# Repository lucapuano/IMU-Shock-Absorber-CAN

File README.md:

# IMU-Shock-Absorber-CAN
Project of an STM32 based module that controll an electromagnet through CAN protocol and get accelerometer and gyroscope data from an IMU

The project has been made on Kicad 5.1.6

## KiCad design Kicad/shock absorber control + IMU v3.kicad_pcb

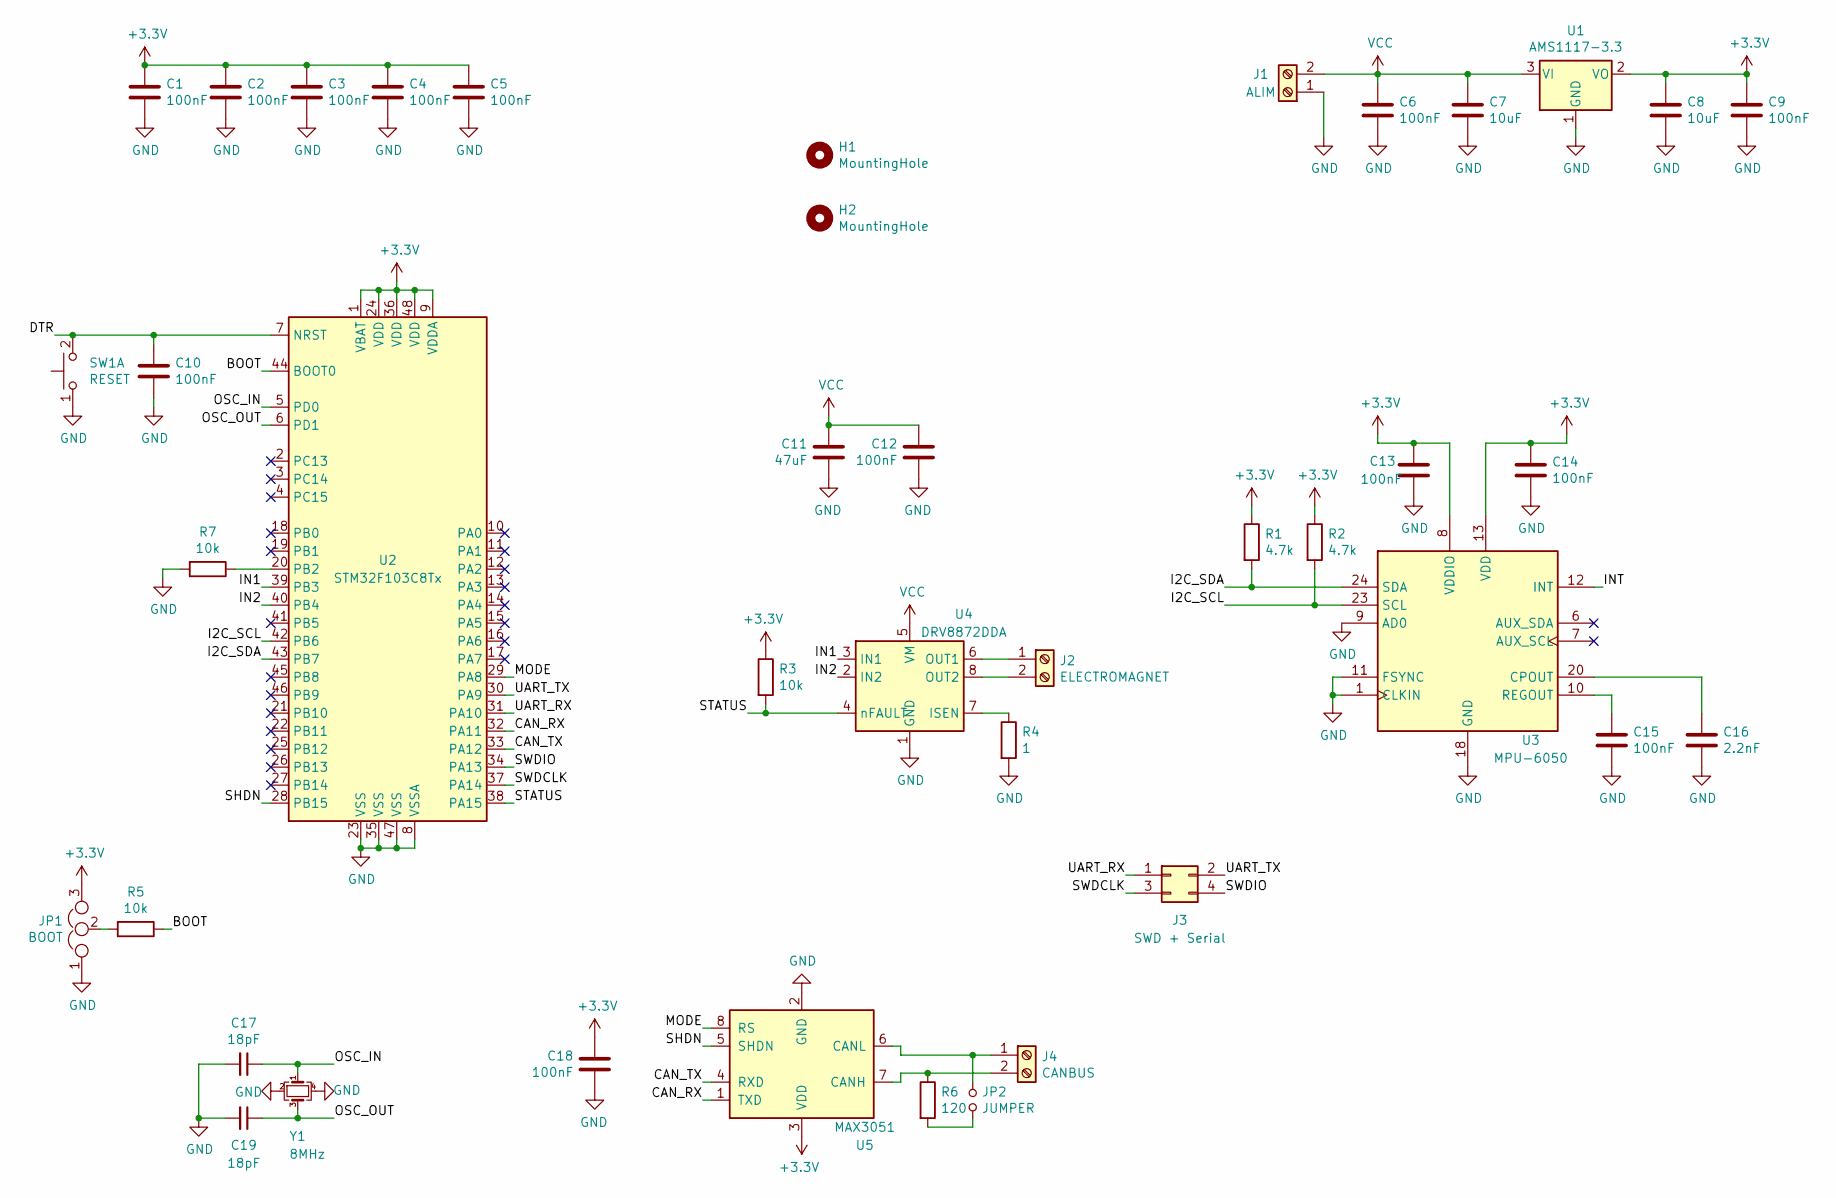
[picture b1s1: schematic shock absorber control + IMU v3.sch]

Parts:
C1, C2, C3, C4, C5, C6, C9, C10, C12, C13, C14, C15, C18: 100nF; C_0603_1608Metric
C7, C8: 10uF; C_0805_2012Metric
C11: 47uF; C_0805_2012Metric
C16: 2.2nF; C_0603_1608Metric
C17, C19: 18pF; C_0603_1608Metric
H1, H2: MountingHole; MountingHole_3mm
J1: ALIM; PinSocket_1x02_P2.54mm_Vertical
J2: ELECTROMAGNET; PinSocket_1x02_P2.54mm_Vertical
J3: SWD + Serial; PinHeader_2x02_P2.54mm_Vertical
J4: CANBUS; PinSocket_1x02_P2.54mm_Vertical
JP1: BOOT; SolderJumper-3_P1.3mm_Open_Pad1.0x1.5mm
JP2: JUMPER; SolderJumper-2_P1.3mm_Open_RoundedPad1.0x1.5mm
R1, R2: 4.7k; R_0603_1608Metric
R3, R5, R7: 10k; R_0603_1608Metric
R4: 1; R_0603_1608Metric
R6: 120; R_0603_1608Metric
SW1: RESET; SW_Push_SPST_NO_Alps_SKRK
U1: AMS1117-3.3; SOT-223-3_TabPin2
U2: STM32F103C8Tx; LQFP-48_7x7mm_P0.5mm
U3: MPU-6050; InvenSense_QFN-24_4x4mm_P0.5mm
U4: DRV8872DDA; HSOP-8-1EP_3.9x4.9mm_P1.27mm_EP2.41x3.1mm_ThermalVias
U5: MAX3051; SOIC-8_3.9x4.9mm_P1.27mm
Y1: 8MHz; Crystal_SMD_Abracon_ABM3C-4Pin_5.0x3.2mm

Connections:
+3V3: C1.1, C2.1, C3.1, C4.1, C5.1, C8.1, C9.1, C13.1, C14.1, C18.1, JP1.3, R1.1, R2.1, R3.1, U1.2 (VO), U2.1 (VBAT), U2.9 (VDDA), U2.24 (VDD), U2.36 (VDD), U2.48 (VDD), U3.8 (VDDIO), U3.13 (VDD), U5.3 (VDD)
/BOOT: R5.1, U2.44 (BOOT0)
/CAN_RX: U2.32 (PA11), U5.1 (TXD)
/CAN_TX: U2.33 (PA12), U5.4 (RXD)
/DTR: C10.1, SW1.2 (D), U2.7 (NRST)
/I2C_SCL: R2.2, U2.42 (PB6), U3.23 (SCL)
/I2C_SDA: R1.2, U2.43 (PB7), U3.24 (SDA)
/IN1: U2.39 (PB3), U4.3 (IN1); also elsewhere on the board
/IN2: U2.40 (PB4), U4.2 (IN2); also elsewhere on the board
/INT: U3.12 (INT)
/MODE: U2.29 (PA8), U5.8 (RS)
/OSC_IN: C17.1, U2.5 (PD0), Y1.1
/OSC_OUT: C19.1, U2.6 (PD1), Y1.3
/SHDN: U2.28 (PB15), U5.5 (SHDN)
/STATUS: R3.2, U2.38 (PA15), U4.4 (nFAULT)
/SWDCLK: J3.3, U2.37 (PA14)
/SWDIO: J3.4, U2.34 (PA13)
/UART_RX: J3.1, U2.31 (PA10)
/UART_TX: J3.2, U2.30 (PA9)
GND: C1.2, C2.2, C3.2, C4.2, C5.2, C6.2, C7.2, C8.2, C9.2, C10.2, C11.2, C12.2, C13.2, C14.2, C15.2, C16.2, C17.2, C18.2, C19.2, J1.1, JP1.1, R4.2, R7.2, SW1.1 (C), U1.1 (GND), U2.8 (VSSA), U2.23 (VSS), U2.35 (VSS), U2.47 (VSS), U3.1 (CLKIN), U3.9 (AD0), U3.11 (FSYNC), U3.18 (GND), U4.1 (GND), U4.9 (GND), U5.2 (GND), Y1.2, Y1.4
unnamed: C15.1, U3.10 (REGOUT)
unnamed: C16.1, U3.20 (CPOUT)
unnamed: J2.1, U4.6 (OUT1)
unnamed: J2.2, U4.8 (OUT2)
unnamed: J4.1, JP2.1, U5.6 (CANL)
unnamed: J4.2, R6.1, U5.7 (CANH)
unnamed: JP1.2, R5.2
unnamed: JP2.2, R6.2
unnamed: R4.1, U4.7 (ISEN)
unnamed: R7.1, U2.20 (PB2)
VCC: C6.1, C7.1, C11.1, C12.1, J1.2, U1.3 (VI), U4.5 (VM)

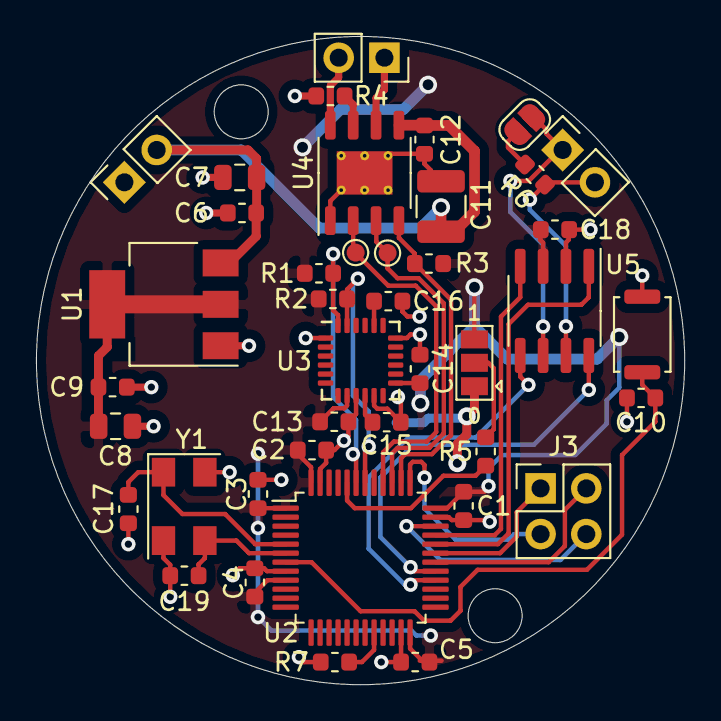
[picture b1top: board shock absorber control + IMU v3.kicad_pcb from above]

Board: 2 copper layers, 36.0 x 36.0 mm, 43 parts (0 on the bottom side), 30 nets.

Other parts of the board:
IN1, IN2: TestPoint_Pad_D1.0mm

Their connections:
/IN1: IN1.1; also elsewhere on the board
/IN2: IN2.1; also elsewhere on the board

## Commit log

2020-10-07 Create lol
